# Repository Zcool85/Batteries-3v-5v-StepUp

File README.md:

# Batteries-3v-5v-StepUp
KiCAD Project for converting 3v (3xAA batteries) to 5V 1A

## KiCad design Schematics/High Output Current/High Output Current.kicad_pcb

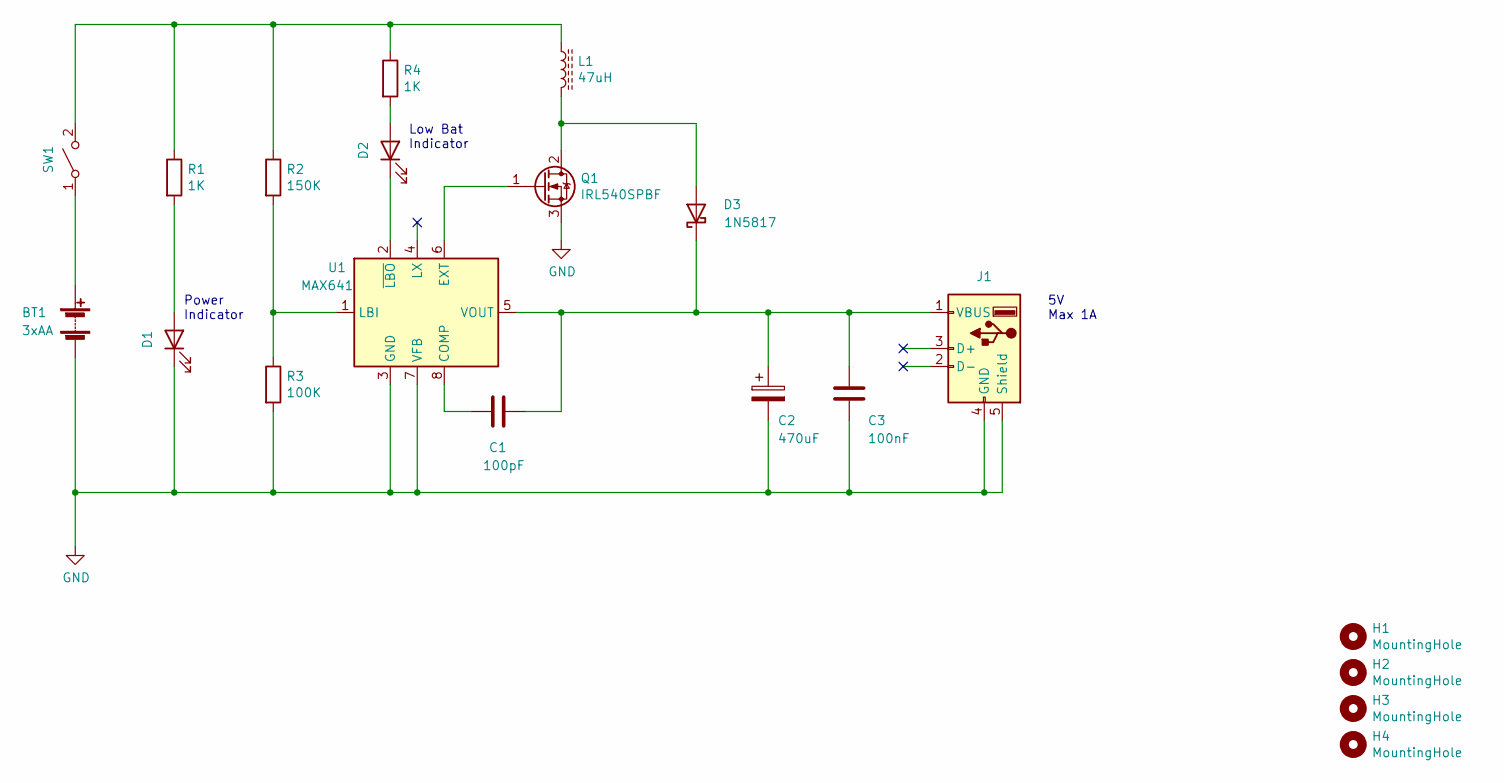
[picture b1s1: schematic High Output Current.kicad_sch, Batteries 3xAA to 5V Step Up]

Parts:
BT1: 3xAA; BatteryHolder_TruPower_BH-331P_3xAA
C1: 100pF; C_Disc_D5.0mm_W2.5mm_P5.00mm
C2: 470uF; CP_Radial_D10.0mm_P5.00mm
C3: 100nF; C_Disc_D5.0mm_W2.5mm_P5.00mm
D1, D2: LED; LED_D3.0mm
D3: 1N5817; D_DO-41_SOD81_P2.54mm_Vertical_AnodeUp
H1, H2, H3, H4: MountingHole; MountingHole_3.5mm
J1: USB_A; USB_A_Stewart_SS-52100-001_Horizontal
L1: 47uH; L_Radial_D9.5mm_P5.00mm_Fastron_07HVP
Q1: IRL540SPBF; TO-263-2
R1, R4: 1K; R_Axial_DIN0207_L6.3mm_D2.5mm_P2.54mm_Vertical
R2: 150K; R_Axial_DIN0207_L6.3mm_D2.5mm_P2.54mm_Vertical
R3: 100K; R_Axial_DIN0207_L6.3mm_D2.5mm_P2.54mm_Vertical
SW1: SW_SPST; PinHeader_1x02_P2.54mm_Horizontal
U1: MAX641; SOIC-8-1EP_3.9x4.9mm_P1.27mm_EP2.514x3.2mm

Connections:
GND: BT1.2 (-), C2.2, C3.2, D1.1 (K), J1.4 (GND), J1.5 (Shield), Q1.3 (S), R3.2, U1.3 (GND), U1.7 (VFB)
unnamed: BT1.1 (+), SW1.1 (A)
unnamed: C1.1, U1.8 (COMP)
unnamed: C1.2, C2.1, C3.1, D3.1 (K), J1.1 (VBUS), U1.5 (VOUT)
unnamed: D1.2 (A), R1.2
unnamed: D2.1 (K), U1.2 (~LBO)
unnamed: D2.2 (A), R4.2
unnamed: D3.2 (A), L1.2, Q1.2 (D)
unnamed: L1.1, R1.1, R2.1, R4.1, SW1.2 (B)
unnamed: Q1.1 (G), U1.6 (EXT)
unnamed: R2.2, R3.1, U1.1 (LBI)

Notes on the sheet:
Low Bat Indicator
5V Max 1A
Power Indicator

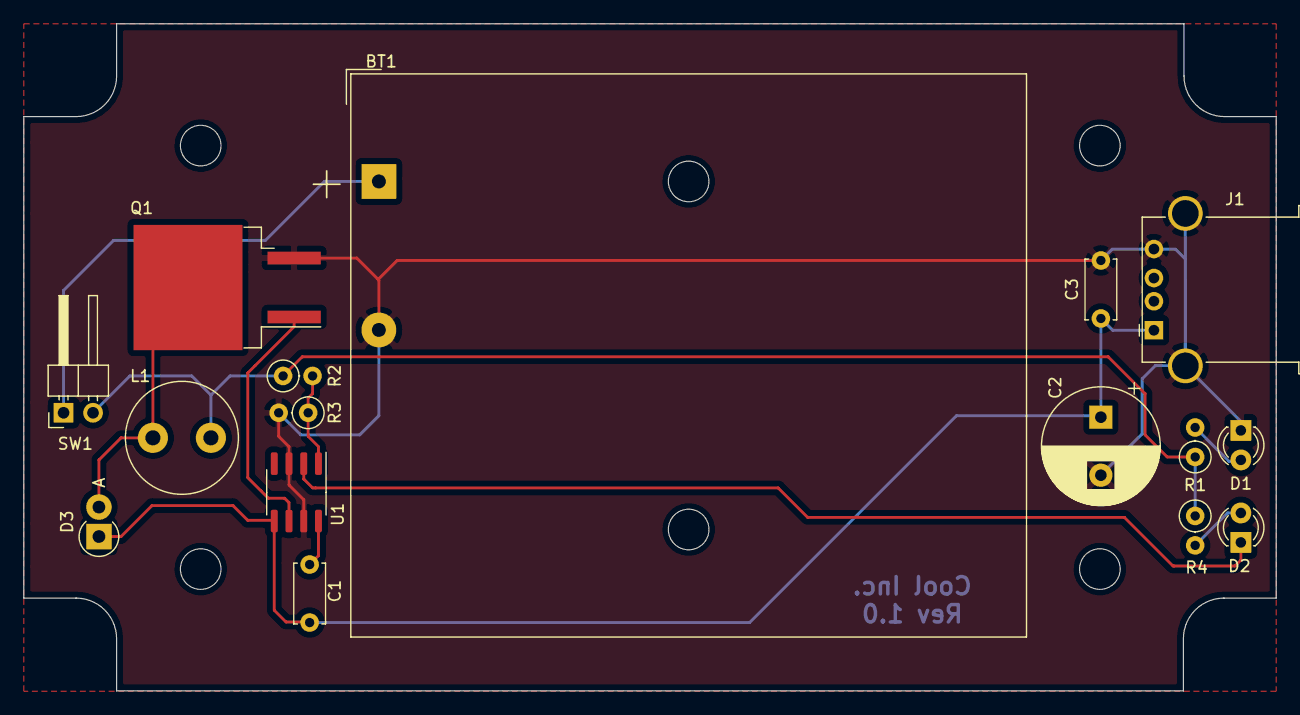
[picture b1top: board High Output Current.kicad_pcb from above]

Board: 2 copper layers, 108.0 x 57.5 mm, 20 parts (0 on the bottom side), 11 nets.

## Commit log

2023-01-22 Add two schematics : High Output Current and Low Power
2023-01-27 Add footprints
2023-01-28 Add PCB design for High Output Current
2023-01-28 Add PCB after gerber files creation
2023-01-28 Switch to KiCad v6
